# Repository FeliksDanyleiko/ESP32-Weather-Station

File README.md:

# ESP32-S3 Weather Station

## Project Overview

This project is an embedded weather station developed for the ELTC H3023 Interfacing Assignment 2026.

The system uses an ESP32-S3 microcontroller to read atmospheric pressure and temperature from a BMP280 sensor and display the results on a TFT screen. A KY-023 joystick will be used to navigate between different pages.

## Hardware

- ESP32-S3-DevKitC-1
- BMP280 Pressure and Temperature Sensor
- GMT020-02-7P TFT Display (ST7789)
- KY-023 Analog Joystick

## Software

- Visual Studio Code
- PlatformIO
- C++
- Git and GitHub

## Development Progress

### Stage 1 — TFT Display
Status: Working

The TFT display has been connected to the ESP32-S3 and tested.

### Stage 2 — BMP280 Sensor
Status: Working

Connect the sensor using I2C and read pressure and temperature measurements.

### Stage 3 — Joystick
Status: Working

Read joystick movements and detect button presses.

### Stage 4 — Menu System
Status: Working

Create an interactive menu with pressure and temperature pages.

### Stage 5 — Elevation Tracking
Status: Working 

Implement sea-level pressure calibration and calculate elevation.

### Stage 6 — Schematic and PCB
Status: Done

Design the circuit schematic and custom PCB layout.

## Git Branches

- `main` — Stable version of the project.

Feature branches will be created as development progresses.

## Project Status

Finished

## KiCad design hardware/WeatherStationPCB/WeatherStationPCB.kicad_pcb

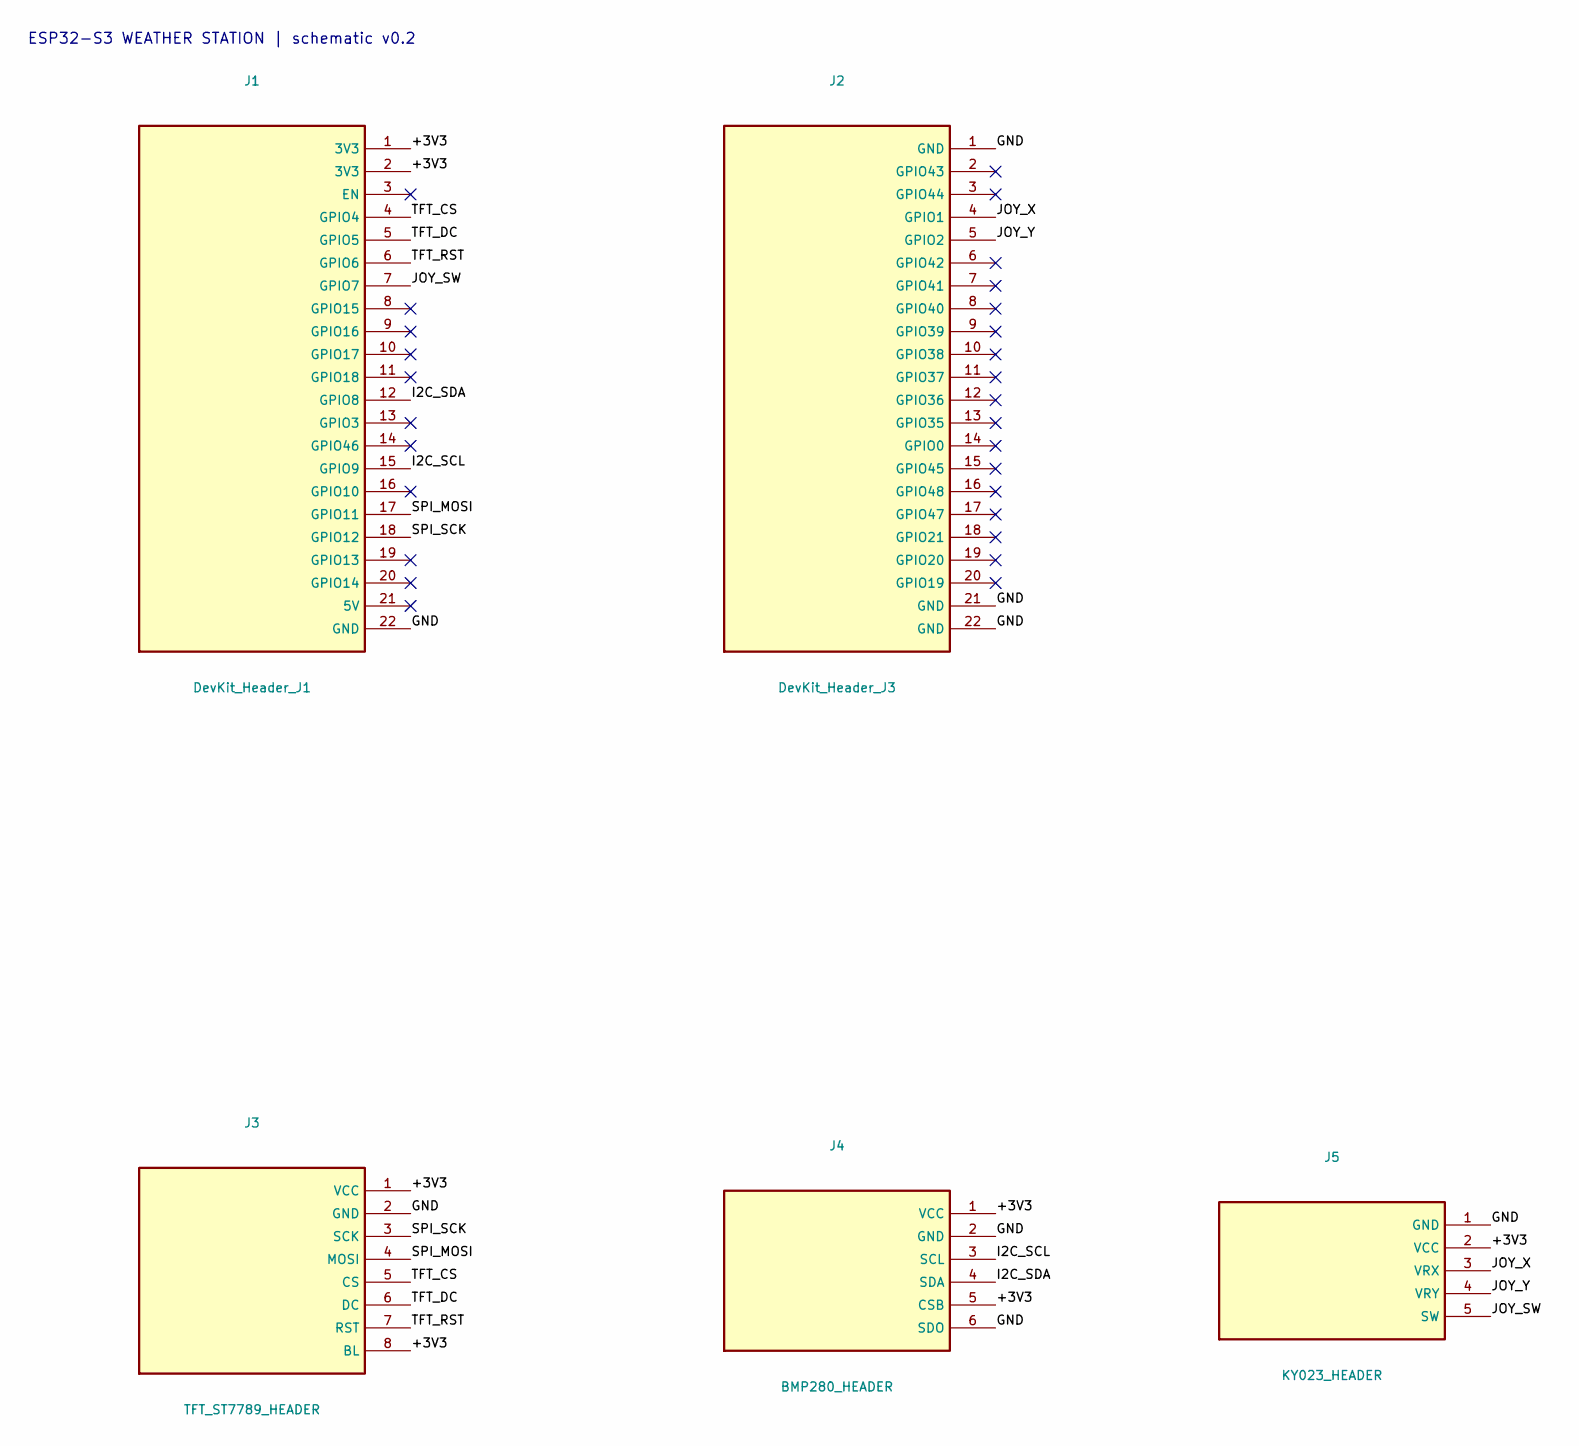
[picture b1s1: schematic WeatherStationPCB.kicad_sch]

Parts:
J1: DevKit_Header_J1; PinHeader_1x22_P2.54mm_Vertical
J2: DevKit_Header_J3; PinHeader_1x22_P2.54mm_Vertical
J3: TFT_ST7789_HEADER; PinHeader_1x08_P2.54mm_Vertical
J4: BMP280_HEADER; PinHeader_1x06_P2.54mm_Vertical
J5: KY023_HEADER; PinHeader_1x05_P2.54mm_Vertical

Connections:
+3V3: J1.1 (3V3), J1.2 (3V3), J3.1 (VCC), J3.8 (BL), J4.1 (VCC), J4.5 (CSB), J5.2 (VCC)
GND: J1.22 (GND), J2.1 (GND), J2.21 (GND), J2.22 (GND), J3.2 (GND), J4.2 (GND), J4.6 (SDO), J5.1 (GND)
I2C_SCL: J1.15 (GPIO9), J4.3 (SCL)
I2C_SDA: J1.12 (GPIO8), J4.4 (SDA)
JOY_SW: J1.7 (GPIO7), J5.5 (SW)
JOY_X: J2.4 (GPIO1), J5.3 (VRX)
JOY_Y: J2.5 (GPIO2), J5.4 (VRY)
SPI_MOSI: J1.17 (GPIO11), J3.4 (MOSI)
SPI_SCK: J1.18 (GPIO12), J3.3 (SCK)
TFT_CS: J1.4 (GPIO4), J3.5 (CS)
TFT_DC: J1.5 (GPIO5), J3.6 (DC)
TFT_RST: J1.6 (GPIO6), J3.7 (RST)

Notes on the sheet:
ESP32-S3 WEATHER STATION | schematic v0.2

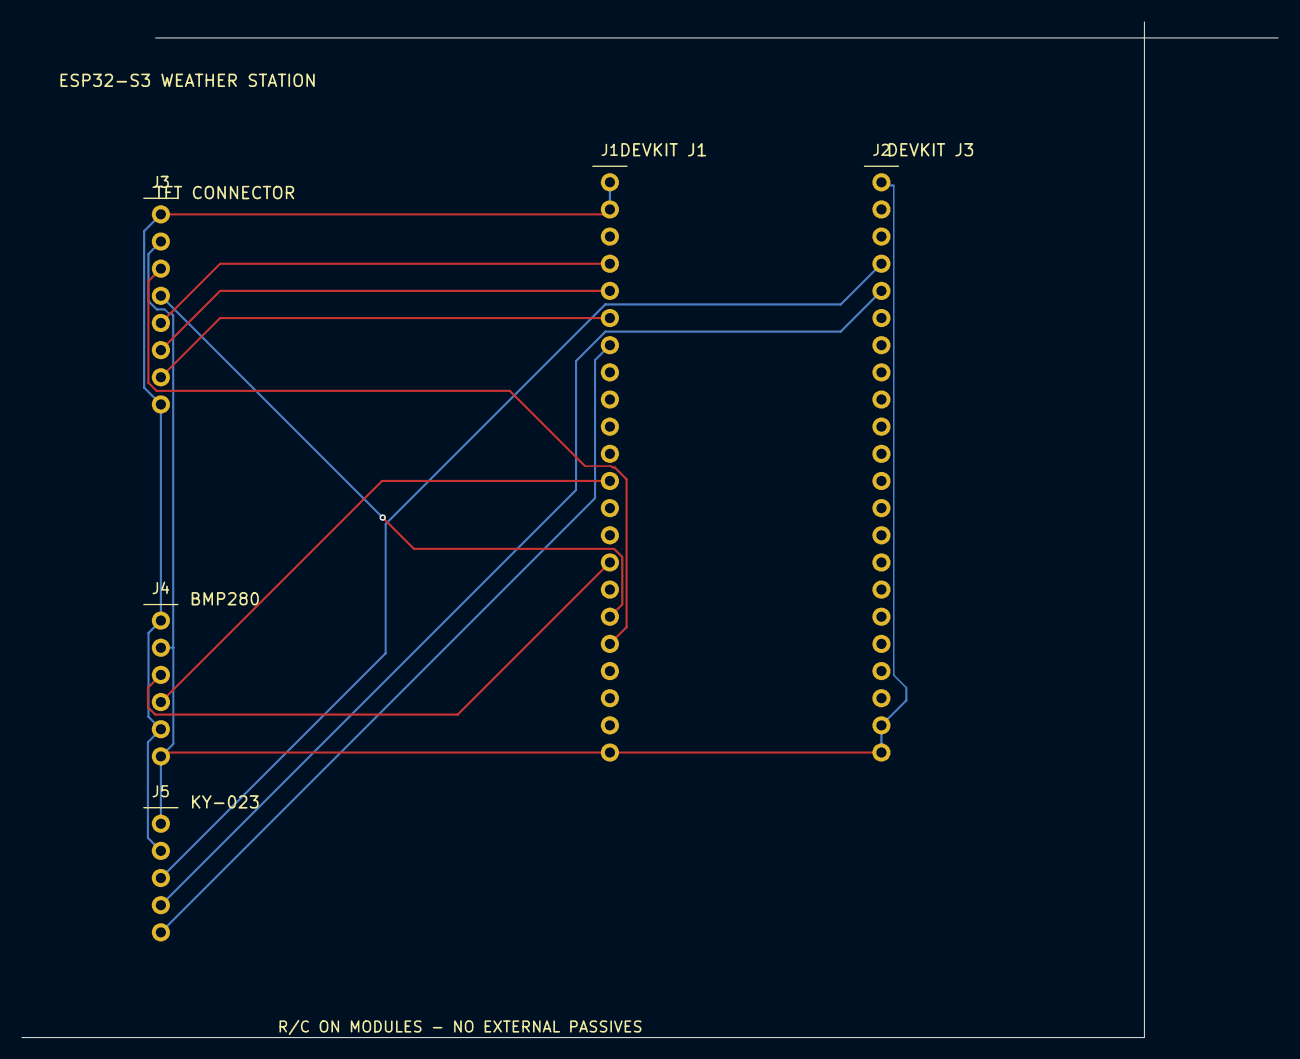
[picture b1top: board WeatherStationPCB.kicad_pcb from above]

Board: 2 copper layers, 117.5 x 95.0 mm, 5 parts (0 on the bottom side), 12 nets.

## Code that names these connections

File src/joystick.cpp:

#include <Arduino.h>
#include "joystick.h"

// Joystick analogue axes and push-button pin
#define JOY_X  1
#define JOY_Y  2
#define JOY_SW 7

bool lastButton = HIGH;
bool stableButton = HIGH;

unsigned long lastDebounce = 0;
unsigned long lastMove = 0;

void initJoystick() {
  // The button is active-low; use the internal pull-up
  pinMode(JOY_SW, INPUT_PULLUP);
  analogReadResolution(12);
}

JoystickAction readJoystick() {
  bool button = digitalRead(JOY_SW);

  // Start debounce timing when the button level changes
  if (button != lastButton) {
    lastDebounce = millis();
  }

  lastButton = button;

  // Accept one press only after the signal is stable for 30 ms
  if (millis() - lastDebounce > 30 && button != stableButton) {
    stableButton = button;
    if (stableButton == LOW) {
      return PRESS;
    }
  }

  // Read the vertical axis of the joystick
  int y = analogRead(JOY_Y);

  // Limit repeated movements to one every 250 ms
  if (millis() - lastMove > 250) {
    if (y < 1000) {
      lastMove = millis();
      return UP;
    }
    else if (y > 3000) {
      lastMove = millis();
      return DOWN;
    }
  }

  // No new button press or joystick movement
  return NONE;
}

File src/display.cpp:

#include <Arduino.h>
#include <Adafruit_GFX.h>
#include <Adafruit_ST7789.h>
#include "display.h"

// TFT control pins and landscape screen size
#define TFT_CS  4
#define TFT_DC  5
#define TFT_RST 6
#define SCREEN_W 320
#define SCREEN_H 240

Adafruit_ST7789 tft(TFT_CS, TFT_DC, TFT_RST);
GFXcanvas16* canvas = nullptr;

// Copy the prepared image from RAM to the TFT
void showFrame() {
  if (canvas) {
    tft.drawRGBBitmap(0, 0, canvas->getBuffer(), SCREEN_W, SCREEN_H);
  }
}

void initDisplay() {
  tft.init(240, 320);
  tft.setRotation(1);

  // Allocate a 16-bit colour framebuffer to reduce flicker
  canvas = new GFXcanvas16(SCREEN_W, SCREEN_H);
  if (!canvas || !canvas->getBuffer()) {
    // Use direct TFT drawing if the buffer cannot be allocated
    delete canvas;
    canvas = nullptr;
    Serial.println("Display buffer unavailable");
  } else {
    Serial.println("Display buffer ready");
  }
}

void drawMenu(int selected) {
  // Draw to the RAM buffer when available, otherwise to the TFT
  Adafruit_GFX& screen = canvas ? (Adafruit_GFX&)*canvas : (Adafruit_GFX&)tft;

  screen.fillScreen(ST77XX_BLACK);
  screen.setTextColor(ST77XX_WHITE);
  screen.setTextSize(2);

  screen.setCursor(20, 20);
  screen.println("WEATHER STATION");
  const char* options[] = {
    "Pressure (hPa)",
    "Pressure (mbar)",
    "Temperature (C)",
    "Elevation"
  };

  // Highlight the selected menu item in yellow
  for (int i = 0; i < 4; i++) {
    screen.setCursor(20, 70 + i * 35);

    if (i == selected) {
      screen.setTextColor(ST77XX_YELLOW);
      screen.print("> ");
    } else {
      screen.setTextColor(ST77XX_WHITE);
      screen.print("  ");
    }

    screen.println(options[i]);
  }

  showFrame();
}

void drawPage(int selected, bool sensorReady, float value) {
  Adafruit_GFX& screen = canvas ? (Adafruit_GFX&)*canvas : (Adafruit_GFX&)tft;

  screen.fillScreen(ST77XX_BLACK);
  screen.setTextColor(ST77XX_WHITE);
  screen.setTextSize(2);
  screen.setCursor(20, 20);
  // Display the title for the selected measurement
  if (selected == 0) {
    screen.println("Pressure (hPa)");
  }
  else if (selected == 1) {
    screen.println("Pressure (mbar)");
  }
  else if (selected == 2) {
    screen.println("Temperature (C)");
  }
  else {
    screen.println("Elevation (m)");
  }

  // Show an error if the sensor failed to initialise
  if (!sensorReady) {
    screen.setCursor(20, 120);
    screen.println("Sensor not found");
    showFrame();
    return;
  }

  // Print the measured value with two decimal places
  screen.setTextSize(3);
  screen.setCursor(20, 120);
  screen.print(value, 2);
  if (selected == 0) {
    screen.println(" hPa");
  }
  else if (selected == 1) {
    screen.println(" mbar");
  }
  else if (selected == 2) {
    screen.println(" C");
  }
  else {
    screen.println(" m");
  }

  showFrame();
}

void drawCalibration(float seaLevelPressure) {
  Adafruit_GFX& screen = canvas ? (Adafruit_GFX&)*canvas : (Adafruit_GFX&)tft;

  screen.fillScreen(ST77XX_BLACK);
  screen.setTextColor(ST77XX_WHITE);
  screen.setTextSize(2);
  screen.setCursor(20, 20);
  screen.println("Elevation Setup");

  screen.setCursor(20, 65);
  screen.println("Pressure at 0 m:");

  // Show the adjustable reference pressure
  screen.setTextColor(ST77XX_YELLOW);
  screen.setTextSize(3);
  screen.setCursor(20, 105);
  screen.print(seaLevelPressure, 2);

  screen.setTextSize(2);
  screen.println(" hPa");

  screen.setTextColor(ST77XX_WHITE);
  screen.setCursor(20, 165);
  screen.println("UP/DOWN: Adjust");

  screen.setCursor(20, 195);
  screen.println("PRESS: Confirm");

  showFrame();
}
